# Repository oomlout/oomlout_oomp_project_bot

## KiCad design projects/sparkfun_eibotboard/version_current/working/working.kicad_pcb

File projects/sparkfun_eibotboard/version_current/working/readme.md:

# OOMP Project  
## EiBotBoard  by sparkfun  
  
oomp key: oomp_projects_flat_sparkfun_eibotboard  
(snippet of original readme)  
  
EiBotBoard  
==========  

[*EiBotBoard (WIG-10025)*](https://www.sparkfun.com/products/10025)  
  
The EiBotBoard (EBB) was originally designed for the Egg-Bot project.   
It is a small (2.2" x 2.2") two channel stepper motor driver board with USB microcontroller.   
It is based on the UBW board and supports all of the commands that the UBW does (for the most part), plus several extra, like stepper motor commands and RC servo output commands.  
  
Repository Contents  
-------------------  
* **/Hardware** - All Eagle design files (.brd, .sch)  
  
License Information  
-------------------  
Distributed as-is; no warranty is given.  
  
_**Note:** This product is a collaboration with Brian Schmalz. A portion of each sales goes back to him for product support and continued development._  
  full source readme at [readme_src.md](readme_src.md)  
  
source repo at: [https://github.com/sparkfun/EiBotBoard](https://github.com/sparkfun/EiBotBoard)  
## Board  

## Schematic  

[schematic pdf](working_schematic.pdf)  
## Images

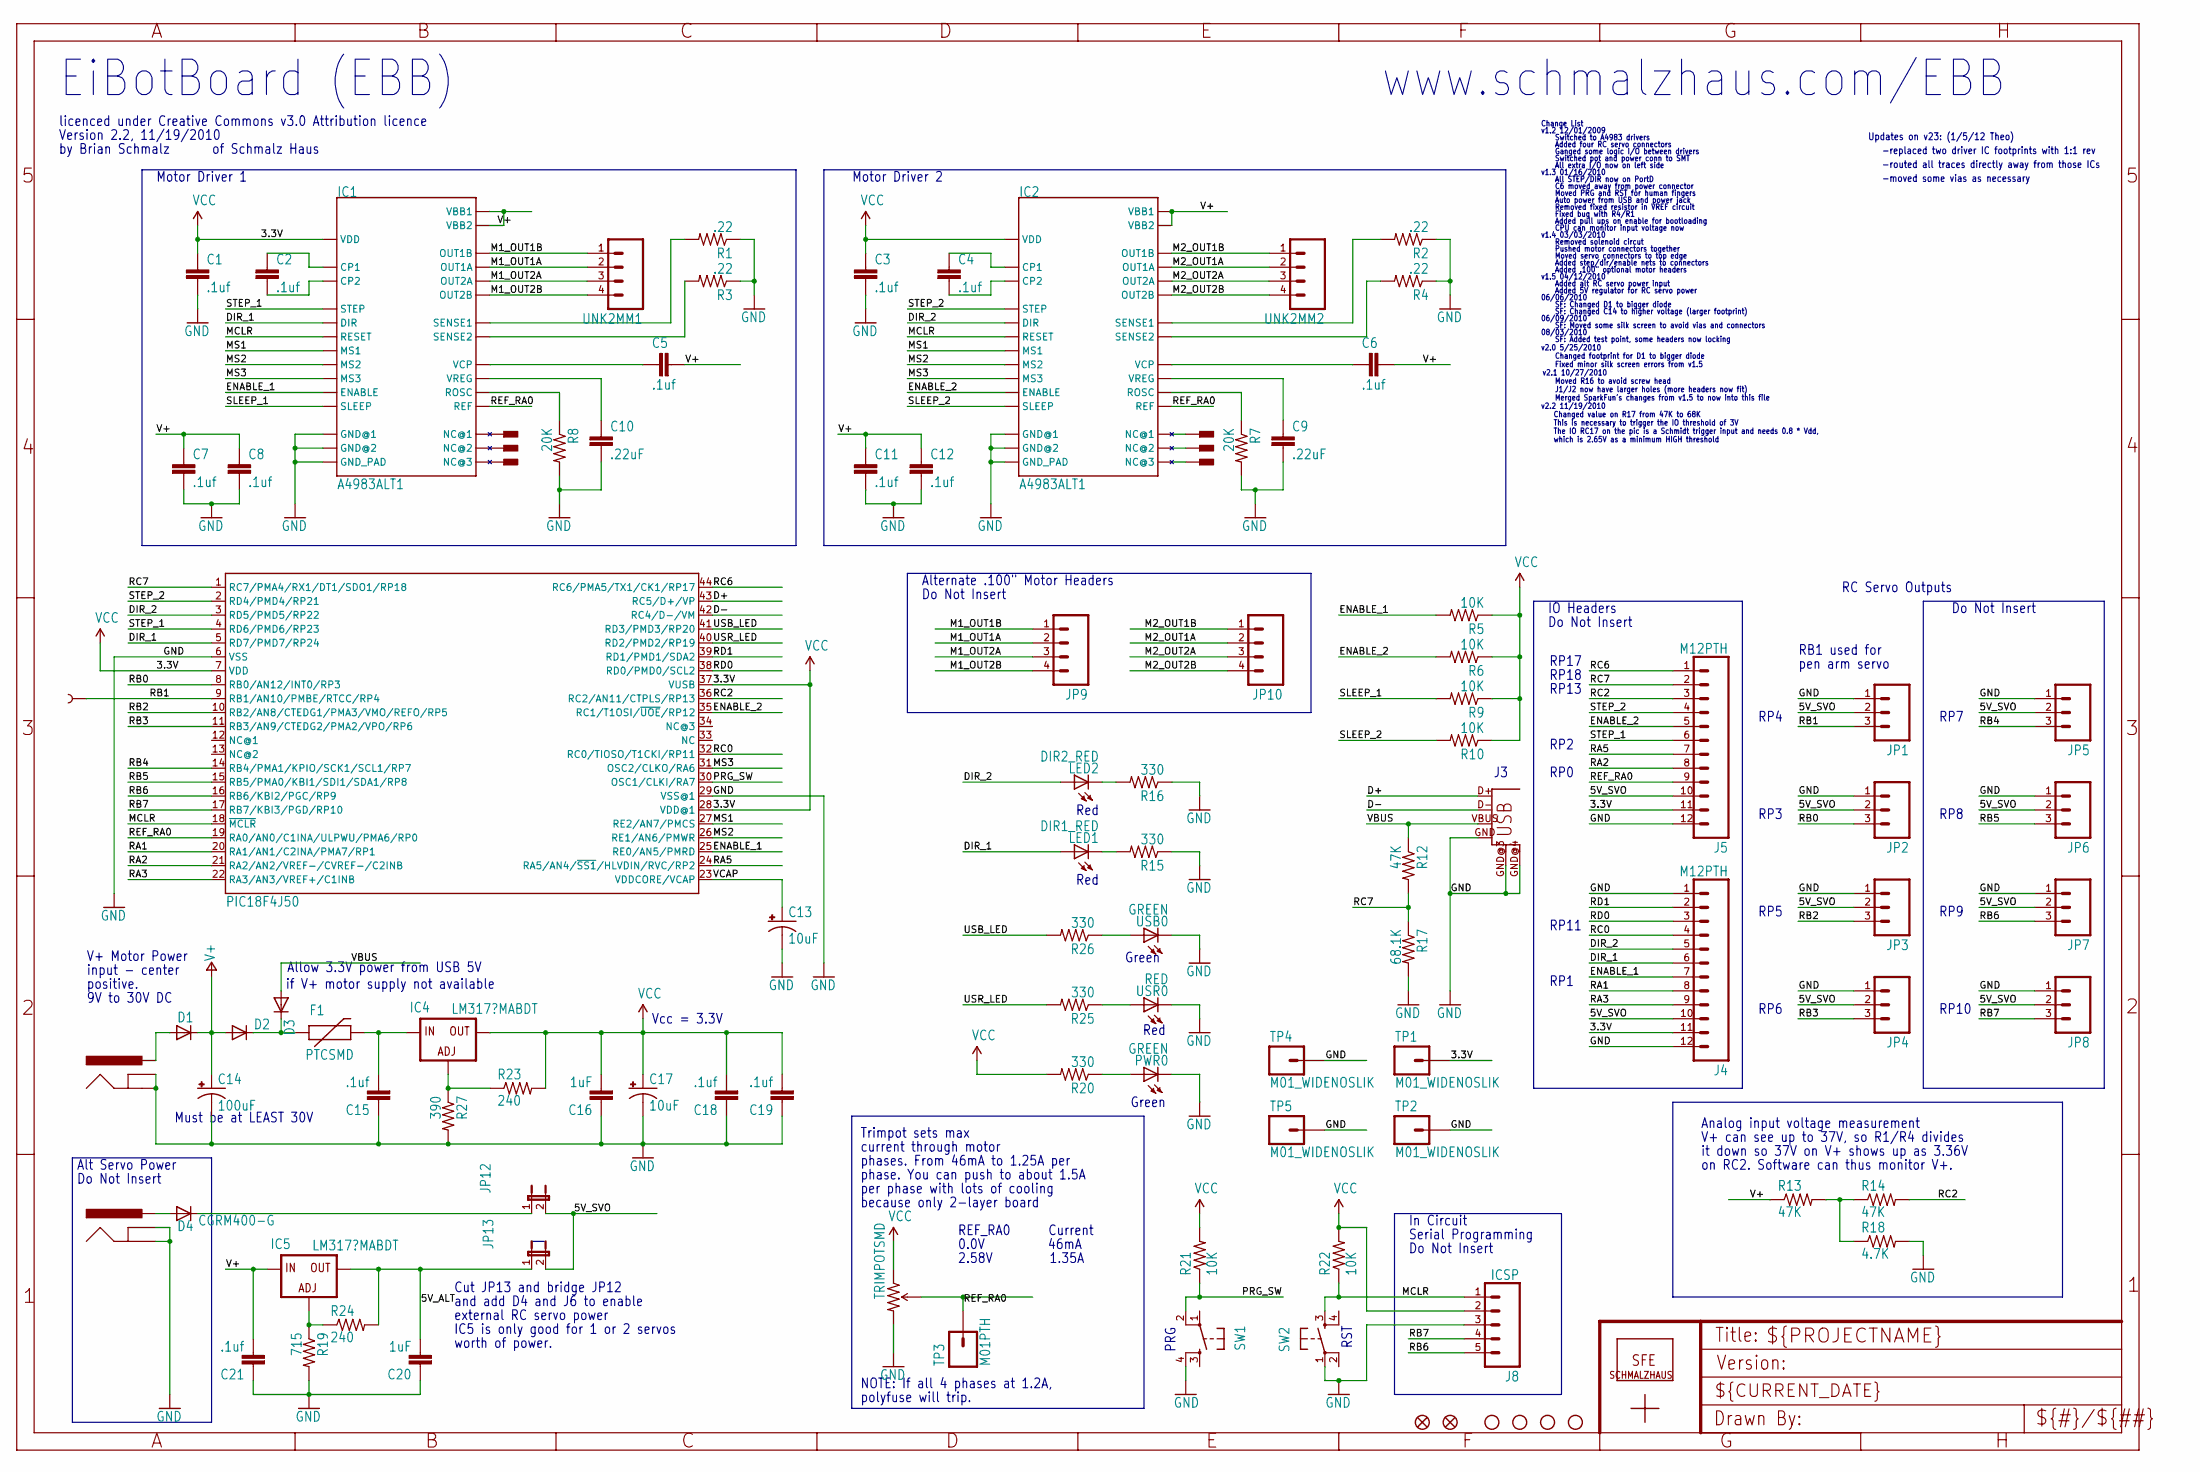
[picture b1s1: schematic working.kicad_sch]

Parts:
C1, C2, C3, C4, C5, C6, C7, C8, C11, C12, C15, C18, C19, C21: .1uf; 0603
C9, C10: .22uF; 0603
C13, C17: 10uF; EIA3216
C14: 100uF; PANASONIC_G
C16, C20: 1uF; 0603
D1: DIODE-DO214AC; DO214AC
D2, D3: DIODESMA; SMA-DIODE
D4: CGRM400-G; SOD-123_MINI-SMA
F1: PTCSMD; PTC-1206
IC1, IC2: A4983ALT1; QFN-28-5MM_ALT1
IC3: PIC18F4J50; TQFP44
IC4, IC5: LM317?MABDT; DPACK
J3: USBSMD; USB-MINIB
J4, J5: M12PTH; 1X12
J6, J7: POWER_JACKSMD; POWER_JACK_SMD
J8: ICSP; 1X05_NOSILK
JP1: M03LOCK_NO_SILK; 1X03_LOCK_NO_SILK
JP2, JP3, JP4, JP5, JP6, JP7, JP8: M031X03_NO_SILK; 1X03_NO_SILK
JP9, JP10: M04POLAR; MOLEX-1X4
JP11: LOGO-SFENEW; SFE-NEW-WEBLOGO
JP12, JP13: JUMPER-2SMD-NO; SJ_2S-NO
JP14, JP15: FIDUCIALUFIDUCIAL; MICRO-FIDUCIAL
LED1: DIR1_RED; LED-0603
LED2: DIR2_RED; LED-0603
PWR0: GREEN; LED-0603
R1, R2, R3, R4: .22; R0805
R5, R6, R9, R10, R21, R22: 10K; R0603
R7, R8: 20K; R0603
R11: TRIMPOTSMD; TRIMPOT-3MM
R12, R13, R14: 47K; R0603
R15, R16, R20, R25, R26: 330; R0603
R17: 68.1K; R0603
R18: 4.7K; R0603
R19: 715; R0603
R23, R24: 240; R0603
R27: 390; R0603
SW1: PRG; TACTILE_SWITCH_SMD
SW2: RST; TACTILE_SWITCH_SMD
TP1, TP2, TP4, TP5: M01_WIDENOSLIK; 1X01_NOSILK
TP3: M01PTH; 1X01
TP6: TEST-POINT3X5; PAD.03X.05
U$1: SCHMALZHAUSSCHMALZHAUS_SMALL; SCHMALZHAUS_SMALL
U$2, U$3, U$4, U$5: STAND-OFF
U$6, U$7, U$8, U$9, U$10, U$11: PAD; PAD-0.008
UNK2MM1, UNK2MM2: SCHMALZHAUS_M04; SCHMALZHAUS_SCREWTERMINAL-3.5MM-4_LOCK
USB0: GREEN; LED-0603
USR0: RED; LED-0603

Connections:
3.3V: C1.1, C3.1, C16.2, C17.A (+), C18.2, C19.2, IC1.P$15 (VDD), IC2.P$15 (VDD), IC3.7 (VDD), IC3.28 (VDD@1), IC3.37 (VUSB), IC4.4 (OUT), J4.11, J5.11, J8.2, R5.1, R6.1, R9.1, R10.1, R11.1 (CCW), R20.2, R21.2, R22.2, R23.2, TP1.1
5V_ALT: C20.2, IC5.4 (OUT), JP13.1, R24.2
5V_SVO: J4.10, J5.10, JP1.2, JP2.2, JP3.2, JP4.2, JP5.2, JP6.2, JP7.2, JP8.2, JP12.2, JP13.2
D+: IC3.43 (RC5/D+/VP), J3.D+
D-: IC3.42 (RC4/D-/VM), J3.D-
DIR_1: IC1.P$19 (DIR), IC3.5 (RD7/PMD7/RP24), J4.6, LED1.A
DIR_2: IC2.P$19 (DIR), IC3.3 (RD5/PMD5/RP22), J4.5, LED2.A
ENABLE_1: IC1.P$2 (ENABLE), IC3.25 (RE0/AN5/PMRD), J4.7, R5.2
ENABLE_2: IC2.P$2 (ENABLE), IC3.35 (RC1/T1OSI/~UOE/RP12), J5.5, R6.2
GND: C1.2, C3.2, C7.2, C8.2, C9.2, C10.2, C11.2, C12.2, C13.C (-), C14.-, C15.1, C16.1, C17.C (-), C18.1, C19.1, C20.1, C21.1, IC1.P$3 (GND@1), IC1.P$18 (GND@2), IC1.P$29 (GND_PAD), IC2.P$3 (GND@1), IC2.P$18 (GND@2), IC2.P$29 (GND_PAD), IC3.6 (VSS), IC3.29 (VSS@1), J3.GND, J3.GND@3 (GND@1), J3.GND@4 (GND@2), J4.1, J4.12, J5.12, J6.GND (GNDBREAK), J6.P$4 (GND), J7.GND (GNDBREAK), J7.P$4 (GND), J8.3, JP1.1, JP2.1, JP3.1, JP4.1, JP5.1, JP6.1, JP7.1, JP8.1, PWR0.C, R1.1, R2.1, R3.1, R4.1, R7.2, R8.2, R11.3 (CW), R15.1, R16.1, R17.2, R18.2, R19.2, R27.2, SW1.4, SW2.1, TP2.1, TP4.1, TP5.1, USB0.C, USR0.C
M1_OUT1A: IC1.P$24 (OUT1A), JP9.2, UNK2MM1.2
M1_OUT1B: IC1.P$21 (OUT1B), JP9.1, UNK2MM1.1
M1_OUT2A: IC1.P$26 (OUT2A), JP9.3, UNK2MM1.3
M1_OUT2B: IC1.P$1 (OUT2B), JP9.4, UNK2MM1.4
M2_OUT1A: IC2.P$24 (OUT1A), JP10.2, UNK2MM2.2
M2_OUT1B: IC2.P$21 (OUT1B), JP10.1, UNK2MM2.1
M2_OUT2A: IC2.P$26 (OUT2A), JP10.3, UNK2MM2.3
M2_OUT2B: IC2.P$1 (OUT2B), JP10.4, UNK2MM2.4
MCLR: IC1.P$12 (RESET), IC2.P$12 (RESET), IC3.18 (~MCLR), J8.1, R22.1, SW2.3
MS1: IC1.P$9 (MS1), IC2.P$9 (MS1), IC3.27 (RE2/AN7/PMCS)
MS2: IC1.P$10 (MS2), IC2.P$10 (MS2), IC3.26 (RE1/AN6/PMWR)
MS3: IC1.P$11 (MS3), IC2.P$11 (MS3), IC3.31 (OSC2/CLKO/RA6)
unnamed: D2.C, D3.C, F1.1
unnamed: C2.1, IC1.P$4 (CP1)
unnamed: R13.2, R14.1, R18.1
unnamed: C2.2, IC1.P$5 (CP2)
unnamed: D1.A, J7.VIN0 (PWR)
unnamed: D4.A, J6.VIN0 (PWR)
unnamed: IC5.1 (ADJ), R19.1, R24.1
unnamed: IC4.1 (ADJ), R23.1, R27.1
unnamed: D4.C, JP12.1
unnamed: IC1.P$7 (NC@1), U$9.P$1
unnamed: IC1.P$20 (NC@2), U$11.P$1
unnamed: IC1.P$25 (NC@3), U$10.P$1
unnamed: IC2.P$7 (NC@1), U$6.P$1
unnamed: IC2.P$20 (NC@2), U$7.P$1
unnamed: C4.1, IC2.P$4 (CP1)
unnamed: C4.2, IC2.P$5 (CP2)
unnamed: IC2.P$25 (NC@3), U$8.P$1
unnamed: IC1.P$13 (ROSC), R8.1
unnamed: C10.1, IC1.P$8 (VREG)
unnamed: C5.1, IC1.P$6 (VCP)
unnamed: LED2.C, R16.2
unnamed: PWR0.A, R20.1
unnamed: R26.1, USB0.A
unnamed: R25.1, USR0.A
unnamed: IC1.P$27 (SENSE2), R3.2
unnamed: IC1.P$23 (SENSE1), R1.2
unnamed: LED1.C, R15.2
unnamed: C15.2, F1.2, IC4.3 (IN)
unnamed: C6.1, IC2.P$6 (VCP)
unnamed: IC2.P$23 (SENSE1), R2.2
unnamed: IC2.P$27 (SENSE2), R4.2
unnamed: C9.1, IC2.P$8 (VREG)
unnamed: IC2.P$13 (ROSC), R7.1
PRG_SW: IC3.30 (OSC1/CLKI/RA7), R21.1, SW1.2
RA1: IC3.20 (RA1/AN1/C2INA/PMA7/RP1), J4.8
RA2: IC3.21 (RA2/AN2/VREF-/CVREF-/C2INB), J5.8
RA3: IC3.22 (RA3/AN3/VREF+/C1INB), J4.9
RA5: IC3.24 (RA5/AN4/~SS1/HLVDIN/RVC/RP2), J5.7
RB0: IC3.8 (RB0/AN12/INT0/RP3), JP2.3
RB1: IC3.9 (RB1/AN10/PMBE/RTCC/RP4), JP1.3, TP6.P$1
RB2: IC3.10 (RB2/AN8/CTEDG1/PMA3/VMO/REFO/RP5), JP3.3
RB3: IC3.11 (RB3/AN9/CTEDG2/PMA2/VPO/RP6), JP4.3
RB4: IC3.14 (RB4/PMA1/KPIO/SCK1/SCL1/RP7), JP5.3
RB5: IC3.15 (RB5/PMA0/KBI1/SDI1/SDA1/RP8), JP6.3
RB6: IC3.16 (RB6/KBI2/PGC/RP9), J8.5, JP7.3
RB7: IC3.17 (RB7/KBI3/PGD/RP10), J8.4, JP8.3
RC0: IC3.32 (RC0/TIOSO/T1CKI/RP11), J4.4
RC2: IC3.36 (RC2/AN11/CTPLS/RP13), J5.3, R14.2
RC6: IC3.44 (RC6/PMA5/TX1/CK1/RP17), J5.1
RC7: IC3.1 (RC7/PMA4/RX1/DT1/SDO1/RP18), J5.2, R12.2, R17.1
RD0: IC3.38 (RD0/PMD0/SCL2), J4.3
RD1: IC3.39 (RD1/PMD1/SDA2), J4.2
REF_RA0: IC1.P$17 (REF), IC2.P$17 (REF), IC3.19 (RA0/AN0/C1INA/ULPWU/PMA6/RP0), J5.9, R11.2 (WIPER), TP3.1
SLEEP_1: IC1.P$14 (SLEEP), R9.2
SLEEP_2: IC2.P$14 (SLEEP), R10.2
STEP_1: IC1.P$16 (STEP), IC3.4 (RD6/PMD6/RP23), J5.6
STEP_2: IC2.P$16 (STEP), IC3.2 (RD4/PMD4/RP21), J5.4
USB_LED: IC3.41 (RD3/PMD3/RP20), R26.2
USR_LED: IC3.40 (RD2/PMD2/RP19), R25.2
V+: C5.2, C6.2, C7.1, C8.1, C11.1, C12.1, C14.+, C21.2, D1.C, D2.A, IC1.P$22 (VBB1), IC1.P$28 (VBB2), IC2.P$22 (VBB1), IC2.P$28 (VBB2), IC5.3 (IN), R13.1
VBUS: D3.A, J3.VBUS, R12.1
VCAP: C13.A (+), IC3.23 (VDDCORE/VCAP)

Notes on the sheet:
This is necessary to trigger the IO threshold of 3V
Change List
CPU can monitor input voltage now
phase. You can push to about 1.5A
06/09/2010
Changed value on R17 from 47K to 68K
Red
Added 5V regulator for RC servo power
RP11
Auto power from USB and power jack
C6 moved away from power connector
Trimpot sets max
Pushed motor connectors together
RB1 used for
licenced under Creative Commons v3.0 Attribution licence
RP8
because only 2-layer board
v2.2 11/19/2010
v1.4 03/03/2010
9V to 30V DC
phases. From 46mA to 1.25A per
www.schmalzhaus.com/EBB
Cut JP13 and bridge JP12
Green
per phase with lots of cooling
Allow 3.3V power from USB 5V
SF: Added test point, some headers now locking
Moved servo connectors to top edge
Serial Programming
v1.3 01/16/2010
IC5 is only good for 1 or 2 servos
Motor Driver 1
RP10
RP13
Do Not Insert
Removed solenoid circut
Added pull ups on enable for bootloading
The IO RC17 on the pic is a Schmidt trigger input and needs 0.8 * Vdd,
v2.1 10/27/2010
external RC servo power

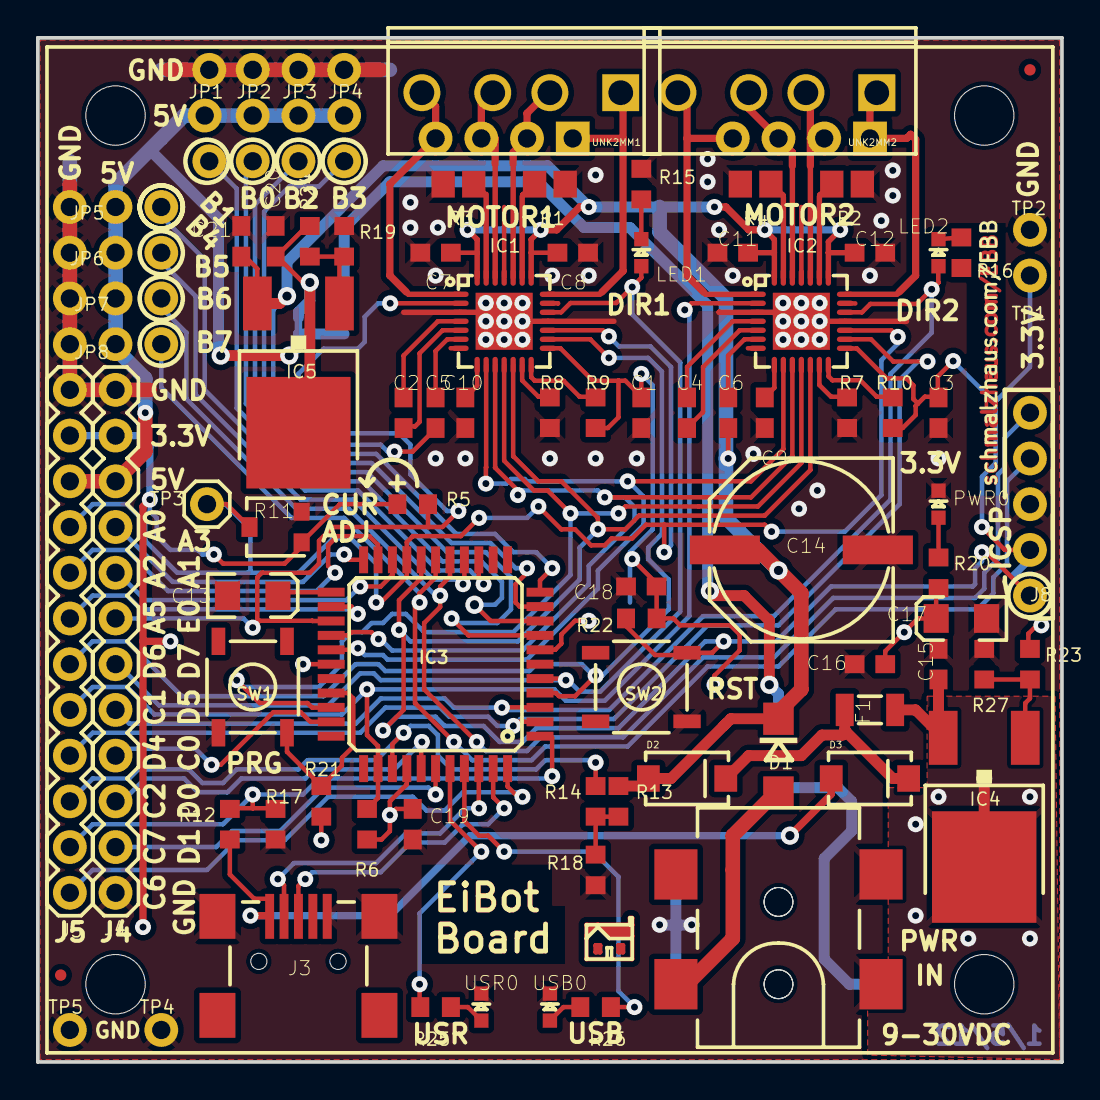
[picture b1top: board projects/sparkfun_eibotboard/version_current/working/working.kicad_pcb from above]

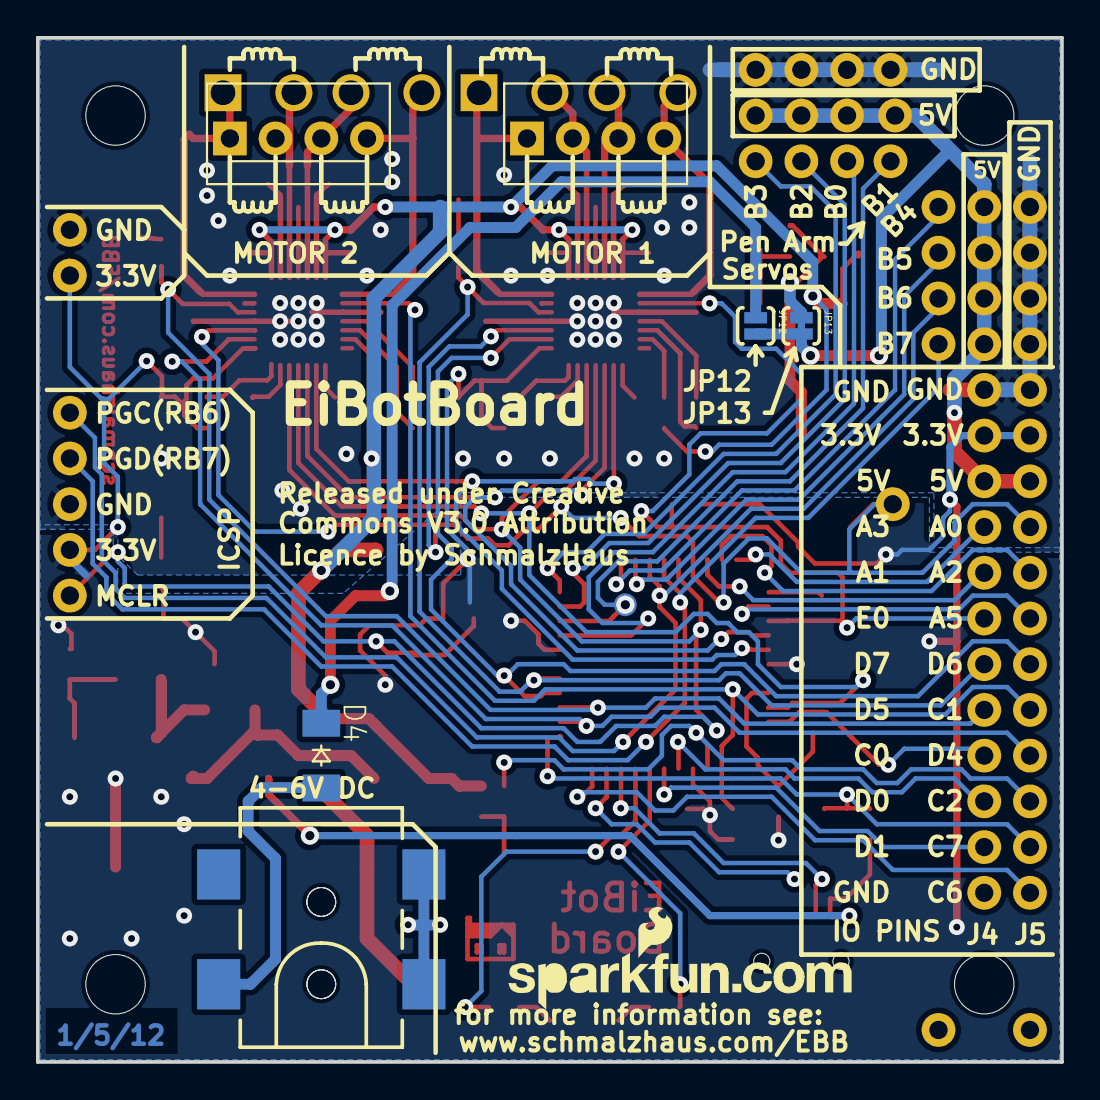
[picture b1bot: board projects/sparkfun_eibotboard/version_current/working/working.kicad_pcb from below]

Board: 2 copper layers, 56.9 x 56.9 mm, 105 parts (8 on the bottom side), 84 nets.

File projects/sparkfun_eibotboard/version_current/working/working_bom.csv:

Row,Description,Part,References,Value,Footprint,Quantity Per PCB,Status,Datasheet
1,,CAP0603,C1 C2 C3 C4 C5 C6 C7 C8 C11 C12 C15 C18 C19 C21,.1uf,0603,14, ,
2,,CAP0603,C9 C10,.22uF,0603,2, ,
3,,CAP0603,C16 C20,1uF,0603,2, ,
4,,CAP_POL1206,C13 C17,10uF,EIA3216,2, ,
5,,SparkFun_CAP_POLG,C14,100uF,PANASONIC_G,1, ,
6,,CGRM400-G,D4,CGRM400-G,SOD-123_MINI-SMA,1, ,
7,,DIODE-DO214AC,D1,DIODE-DO214AC,DO214AC,1, ,
8,,DIODESMA,D2 D3,DIODESMA,SMA-DIODE,2, ,
9,,PTCSMD,F1,PTCSMD,PTC-1206,1, ,
10,,A4983ALT1,IC1 IC2,A4983ALT1,QFN-28-5MM_ALT1,2, ,
11,,LM317?MABDT,IC4 IC5,LM317?MABDT,DPACK,2, ,
12,,PIC18F4J50,IC3,PIC18F4J50,TQFP44,1, ,
13,,M05_WIDENOSILK,J8,ICSP,1X05_NOSILK,1, ,
14,,M12PTH,J4 J5,M12PTH,1X12,2, ,
15,,POWER_JACKSMD,J6 J7,POWER_JACKSMD,POWER_JACK_SMD,2, ,
16,,USBSMD,J3,USBSMD,USB-MINIB,1, ,
17,,JUMPER-2SMD-NO,JP12 JP13,JUMPER-2SMD-NO,SJ_2S-NO,2, ,
18,,LOGO-SFENEW,JP11,LOGO-SFENEW,SFE-NEW-WEBLOGO,1, ,
19,,M031X03_NO_SILK,JP2 JP3 JP4 JP5 JP6 JP7 JP8,M031X03_NO_SILK,1X03_NO_SILK,7, ,
20,,M03LOCK_NO_SILK,JP1,M03LOCK_NO_SILK,1X03_LOCK_NO_SILK,1, ,
21,,M04POLAR,JP9 JP10,M04POLAR,MOLEX-1X4,2, ,
22,,LED0603,LED1,DIR1_RED,LED-0603,1, ,
23,,LED0603,LED2,DIR2_RED,LED-0603,1, ,
24,,LED0603,PWR0 USB0,GREEN,LED-0603,2, ,
25,,R-US_R0805,R1 R2 R3 R4,.22,R0805,4, ,
26,,R-US_R0603,R23 R24,240,R0603,2, ,
27,,R-US_R0603,R15 R16 R20 R25 R26,330,R0603,5, ,
28,,R-US_R0603,R27,390,R0603,1, ,
29,,R-US_R0603,R19,715,R0603,1, ,
30,,R-US_R0603,R18,4.7K,R0603,1, ,
31,,R-US_R0603,R5 R6 R9 R10 R21 R22,10K,R0603,6, ,
32,,R-US_R0603,R7 R8,20K,R0603,2, ,
33,,R-US_R0603,R12 R13 R14,47K,R0603,3, ,
34,,R-US_R0603,R17,68.1K,R0603,1, ,
35,,TRIMPOTSMD,R11,TRIMPOTSMD,TRIMPOT-3MM,1, ,
36,,TAC_SWITCHSND,SW1,PRG,TACTILE_SWITCH_SMD,1, ,
37,,TAC_SWITCHSND,SW2,RST,TACTILE_SWITCH_SMD,1, ,
38,,PAD,U$6 U$7 U$8 U$9 U$10 U$11,PAD,PAD-0.008,6, ,
39,,SCHMALZHAUSSCHMALZHAUS_SMALL,U$1,SCHMALZHAUSSCHMALZHAUS_SMALL,SCHMALZHAUS_SMALL,1, ,
40,,STAND-OFF,U$2 U$3 U$4 U$5,STAND-OFF,STAND-OFF,4, ,
41,,SCHMALZHAUS_M04,UNK2MM1 UNK2MM2,SCHMALZHAUS_M04,SCHMALZHAUS_SCREWTERMINAL-3.5MM-4_LOCK,2, ,
42,,LED0603,USR0,RED,LED-0603,1, ,





Project info:
Schematic:,working
Variant:,default
Revision:,
Date:,2023-08-06_12-56-01
KiCad Version:,7.0.6-7.0.6~ubuntu22.04.1
Statistics:
Component Groups:,42
Component Count:,97 (0 SMD/ 0 THT)
Fitted Components:,97 (0 SMD/ 0 THT)
Number of PCBs:,1
Total Components:,97

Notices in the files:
projects/sparkfun_el_escudo_dos/version_current/working/working.kicad_sch:
http://creativecommons.org/licenses/by-sa/3.0
Released under the Creative Commons Attribution Share-Alike 3.0 License
projects/sparkfun_electric_imp_breakout/version_current/working/working.kicad_sch:
https://creativecommons.org/licenses/by-sa/3.0
parts and their libraries:
Released under the Creative Commons Attribution Share-Alike 4.0 License
